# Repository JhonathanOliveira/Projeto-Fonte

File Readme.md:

# Projeto de uma Fonte - SSC0180 Eletrônica para Computação - USP São Carlos
## Trabalho desenvolvido pelos alunos:
* Jhonathan Oliveira Alves
* João Gabriel Sasseron Roberto Amorim
* Laura Ferré Scotelari
* Samuel Figueiredo Veronez
## Objetivo
Projetar uma fonte que receba uma tensão RMS de 127V de corrente alternada com 60Hz e tenha como saída uma corrente continua constante de tensão ajustável entre 3V a 12V com capacidade de 100mA. O projeto é dividido basicamente em quatro partes.
### 1. Transformador
Adequa o nível de tensão proveniente da rede para o nível de tensão desejada.

### 2. Retificação
Transforma a corrente que antes era alternada em uma corrente continua pulsante através da "transformação" dos semiciclos negativos em positivos usando uma Ponte de Diodos.

### 3. Filtragem
Atenua os "vales" que podem ser vistos no gráfico, para isso usamos um Capacitor. O Ripple é o novo valor da oscilação da tensão e é medido em porcentagem da oscilação original.

### 4. Regulação
Essa é a ultima etapa e consiste em tornar a corrente continua em constante, para isso vamos "cortar" a parte abaixo do pico mínimo do ripple usando um Diodo Zener, dessa forma não teremos mais oscilações. Nesta etapa também vamos tornar a tensão ajustável usando um Potenciômetro e um Transistor.

## O Circuito
### - No Falstad

[Link para o circuito](https://tinyurl.com/yfn5k49m).
### - Esquemático no EAGLE

### - PCB no EAGLE

## Vídeo explicativo dos componentes, valores e circuito
[Link para o vídeo](https://youtu.be/xUj1-Ha36Bw)
## Componentes usados e Preços
|Quant |Componente   |Especificações| Preço     |
|  :-: |     :-:     |     :-:      |    :-:    |
|1x    |[Transformador](https://produto.mercadolivre.com.br/MLB-1590579363-transformador-entrada-110220v-saida-17v-08a-uso-geral-_JM?matt_tool=68186480&matt_word=&matt_source=google&matt_campaign_id=12271057348&matt_ad_group_id=117812253976&matt_match_type=&matt_network=g&matt_device=c&matt_creative=496856058221&matt_keyword=&matt_ad_position=&matt_ad_type=pla&matt_merchant_id=263976801&matt_product_id=MLB1590579363&matt_product_partition_id=310938601101&matt_target_id=pla-310938601101&gclid=Cj0KCQjw9O6HBhCrARIsADx5qCREHJpLEsr8eBNputJEzBJEYFnZsiGpf34z5qbYUBKQijr2rzcTeGgaAiE9EALw_wcB)|    17V       | R$18,91|
|4x    |[Diodo](https://www.baudaeletronica.com.br/diodo-1n4007.html)        |     1N4007   |  R$0,40|
|1x|[Resistor](https://www.baudaeletronica.com.br/resistor-1k-5-1-4w.html?gclid=Cj0KCQjw9O6HBhCrARIsADx5qCRMlNaP_h1QmebZCefj1KAM79iml9dh2ZtkulPFpoBmj30TD4UAbPMaAuWsEALw_wcB)|1k|R$0,06|
|1x|[Resistor](https://www.baudaeletronica.com.br/resistor-2k-5-1-4w.html?gclid=Cj0KCQjw9O6HBhCrARIsADx5qCTXI_57t8omr_wWqVsbYg5ANadbM-3vJB5mD54eyXh_OoTI7aAWtaMaAtXAEALw_wcB)|2k|R$0,06|
|1x|[Capacitor](https://www.baudaeletronica.com.br/capacitor-eletrolitico-1000uf-25v.html?gclid=CjwKCAjwo4mIBhBsEiwAKgzXOPkUna2m2LorTGh_l0Gg98YCBQdBkTDlO88mYA_KzbuIrVka1NLfCRoCCNMQAvD_BwE)|740uF|R$0,88|
|1x|[Potenciômetro](https://www.baudaeletronica.com.br/potenciometro-linear-de-5k-5000.html)|5k|R$2,21|
|1x|[Transistor](https://www.baudaeletronica.com.br/transistor-npn-bc548.html)|NPN|R$0,19|
|1x    |  [Diodo Zener](https://www.baudaeletronica.com.br/diodo-zener-1n4743-13v-1w.html)|  13V  |R$0,21     |
| **Total**   | |             |**R$22,92**|

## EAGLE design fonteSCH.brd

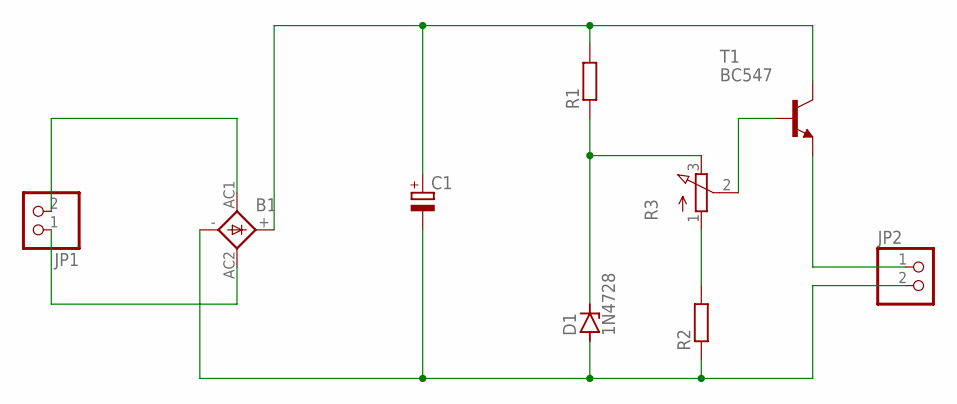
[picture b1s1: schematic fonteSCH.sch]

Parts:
B1: 1KAB
C1: CPOL-EUE5-10.5; E5-10,5
D1: 1N4728; DO41Z10
JP1, JP2: PINHD-1X2; 1X02
R1, R2: R-EU_0207/10; 0207/10
R3: 3RP/1610N
T1: BC547; TO92

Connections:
unnamed: B1.AC1, JP1.2
unnamed: B1.AC2, JP1.1
unnamed: B1.-, C1.-, D1.A, JP2.2, R2.1
unnamed: B1.+, C1.+, R1.2, T1.3 (C)
unnamed: D1.C, R1.1, R3.3 (E)
unnamed: R2.2, R3.1 (A)
unnamed: R3.2 (S), T1.2 (B)
unnamed: JP2.1, T1.1 (E)

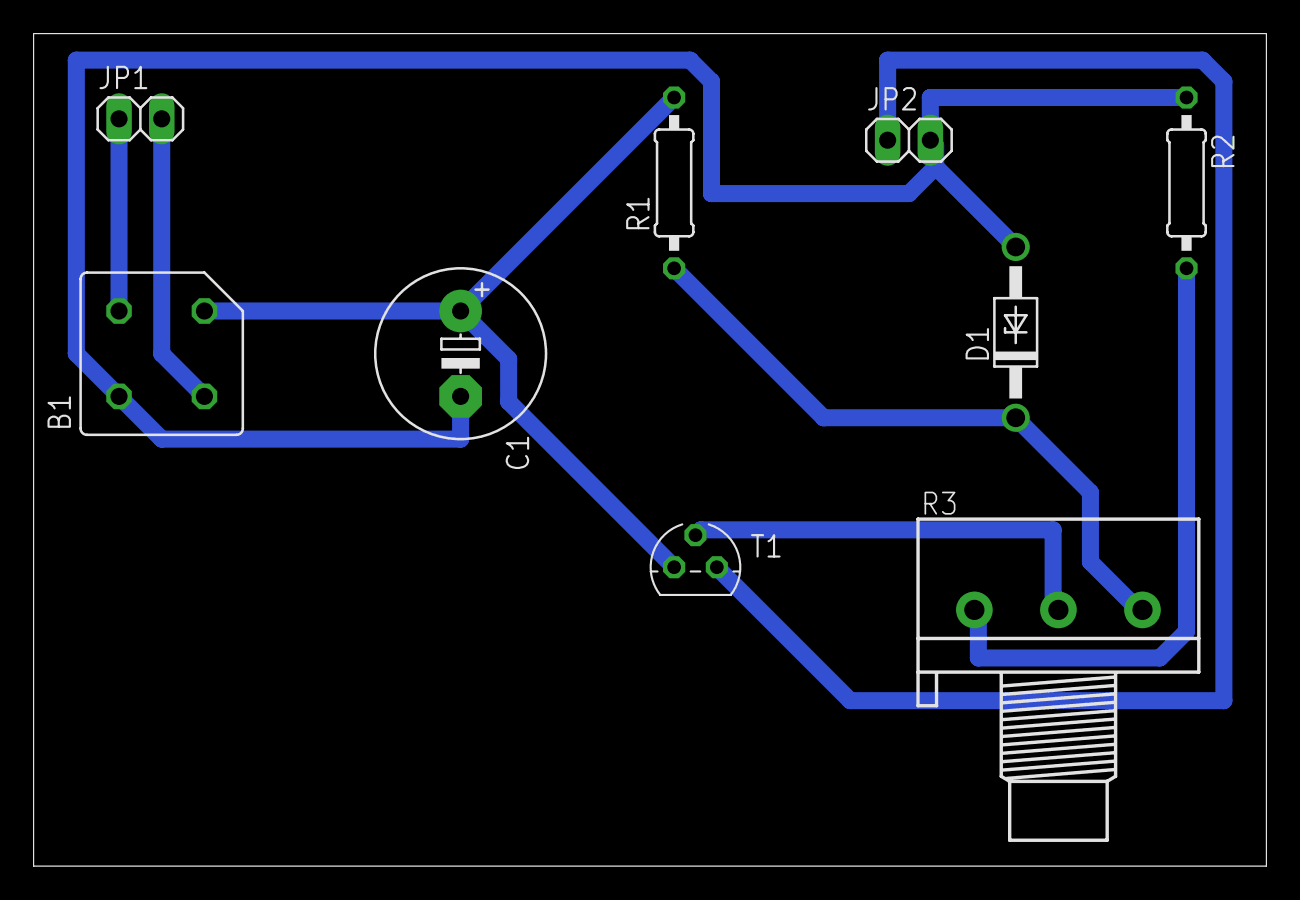
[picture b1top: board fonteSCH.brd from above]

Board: 2 copper layers, 73.3 x 49.5 mm, 9 parts (0 on the bottom side), 8 nets.
